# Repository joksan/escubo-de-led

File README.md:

# escubo-de-led
Un cubo de LED RGB de 4x4x4 en formato de escudo de Arduino

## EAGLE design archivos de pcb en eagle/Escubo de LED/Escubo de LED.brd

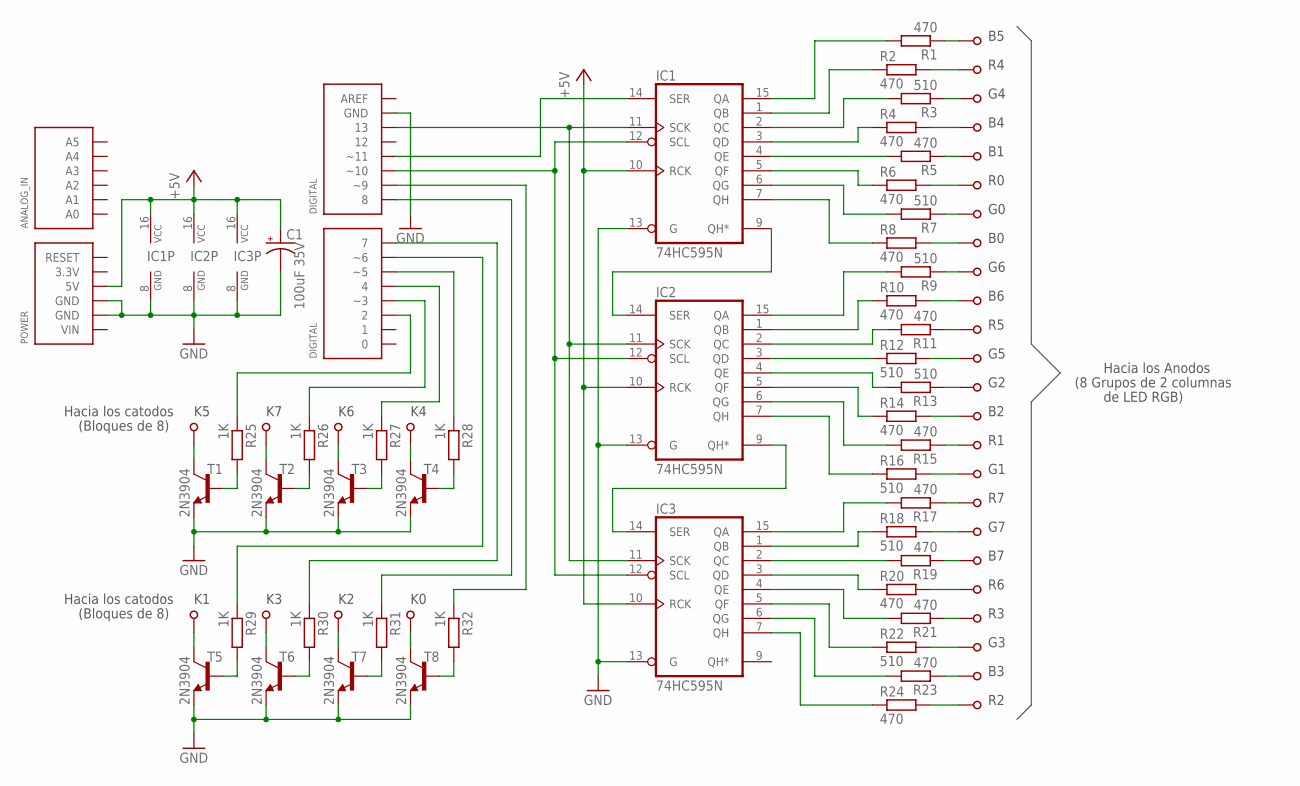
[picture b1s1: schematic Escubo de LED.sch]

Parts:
C1: 100uF 35V; E3,5-8
IC1, IC2, IC3: 74HC595N; DIP16
R1, R2, R4, R10, R11, R15, R17, R19, R20, R23: 470; 0204/7
R3, R7, R9, R12, R18: 510; 0204/7
R5, R21: 470; 0207/12
R6, R14: 470; 0207/10
R8, R24: 470; 0204/5
R13: 510; 0207/12
R16: 510; 0204/5
R22: 510; 0207/10
R25, R26, R27, R28, R29, R30, R31, R32: 1K; 0204V
S1: ARDUINO_SHIELD
T1, T2, T3, T4, T5, T6, T7, T8: 2N3904; TO92-EBC
U$1, U$2, U$3, U$4, U$5, U$6, U$7, U$8, U$9, U$10, U$11, U$12, U$13, U$14, U$15, U$16, U$17, U$18, U$19, U$20, U$21, U$22, U$23, U$24, U$25, U$26, U$27, U$28, U$29, U$30, U$31, U$32: PAD_SIMPLE_PTH

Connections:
+5V: C1.+, IC1.10 (RCK), IC1.16 (VCC), IC2.10 (RCK), IC2.16 (VCC), IC3.10 (RCK), IC3.16 (VCC), S1.5V
GND: C1.-, IC1.8 (GND), IC1.13 (G), IC2.8 (GND), IC2.13 (G), IC3.8 (GND), IC3.13 (G), S1.GND, S1.GND@1 (GND), S1.GND@2 (GND), T1.E, T2.E, T3.E, T4.E, T5.E, T6.E, T7.E, T8.E
unnamed: IC1.9 (QH*), IC2.14 (SER)
unnamed: IC2.9 (QH*), IC3.14 (SER)
unnamed: IC1.11 (SCK), IC2.11 (SCK), IC3.11 (SCK), S1.13
unnamed: IC1.14 (SER), S1.~11
unnamed: IC1.12 (SCL), IC2.12 (SCL), IC3.12 (SCL), S1.~10
unnamed: IC1.15 (QA), R1.2
unnamed: IC1.1 (QB), R2.1
unnamed: IC1.2 (QC), R3.2
unnamed: IC1.3 (QD), R4.1
unnamed: IC1.4 (QE), R5.2
unnamed: IC1.5 (QF), R6.1
unnamed: IC1.6 (QG), R7.2
unnamed: IC1.7 (QH), R8.1
unnamed: IC2.15 (QA), R9.2
unnamed: IC2.1 (QB), R10.1
unnamed: IC2.2 (QC), R11.2
unnamed: IC2.3 (QD), R12.1
unnamed: IC2.4 (QE), R13.2
unnamed: IC2.5 (QF), R14.1
unnamed: IC2.6 (QG), R15.2
unnamed: IC2.7 (QH), R16.1
unnamed: IC3.15 (QA), R17.2
unnamed: IC3.1 (QB), R18.1
unnamed: IC3.2 (QC), R19.2
unnamed: IC3.3 (QD), R20.1
unnamed: IC3.4 (QE), R21.2
unnamed: IC3.5 (QF), R22.1
unnamed: IC3.6 (QG), R23.2
unnamed: IC3.7 (QH), R24.1
unnamed: R1.1, U$1.P$1
unnamed: R2.2, U$2.P$1
unnamed: R3.1, U$3.P$1
unnamed: R4.2, U$4.P$1
unnamed: R6.2, U$6.P$1
unnamed: R8.2, U$8.P$1
unnamed: R10.2, U$10.P$1
unnamed: R12.2, U$12.P$1
unnamed: R14.2, U$14.P$1
unnamed: R16.2, U$16.P$1
unnamed: R18.2, U$18.P$1
unnamed: R20.2, U$20.P$1
unnamed: R22.2, U$22.P$1
unnamed: R24.2, U$24.P$1
unnamed: R5.1, U$5.P$1
unnamed: R7.1, U$7.P$1
unnamed: R9.1, U$9.P$1
unnamed: R11.1, U$11.P$1
unnamed: R13.1, U$13.P$1
unnamed: R15.1, U$15.P$1
unnamed: R17.1, U$17.P$1
unnamed: R19.1, U$19.P$1
unnamed: R21.1, U$21.P$1
unnamed: R23.1, U$23.P$1
unnamed: R25.1, S1.2
unnamed: R26.1, S1.~3
unnamed: R27.1, S1.4
unnamed: R28.1, S1.~5
unnamed: R29.1, S1.~6
unnamed: R30.1, S1.7
unnamed: R31.1, S1.8
unnamed: R32.1, S1.~9
unnamed: T1.C, U$25.P$1
unnamed: T2.C, U$26.P$1
unnamed: T3.C, U$27.P$1
unnamed: T4.C, U$28.P$1
unnamed: T5.C, U$29.P$1
unnamed: T6.C, U$30.P$1
unnamed: T7.C, U$31.P$1
unnamed: T8.C, U$32.P$1
unnamed: R25.2, T1.B
unnamed: R26.2, T2.B
unnamed: R27.2, T3.B
unnamed: R28.2, T4.B
unnamed: R29.2, T5.B
unnamed: R30.2, T6.B
unnamed: R31.2, T7.B
unnamed: R32.2, T8.B

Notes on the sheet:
Hacia los catodos
(Bloques de 8)
Hacia los Anodos
(8 Grupos de 2 columnas
de LED RGB)

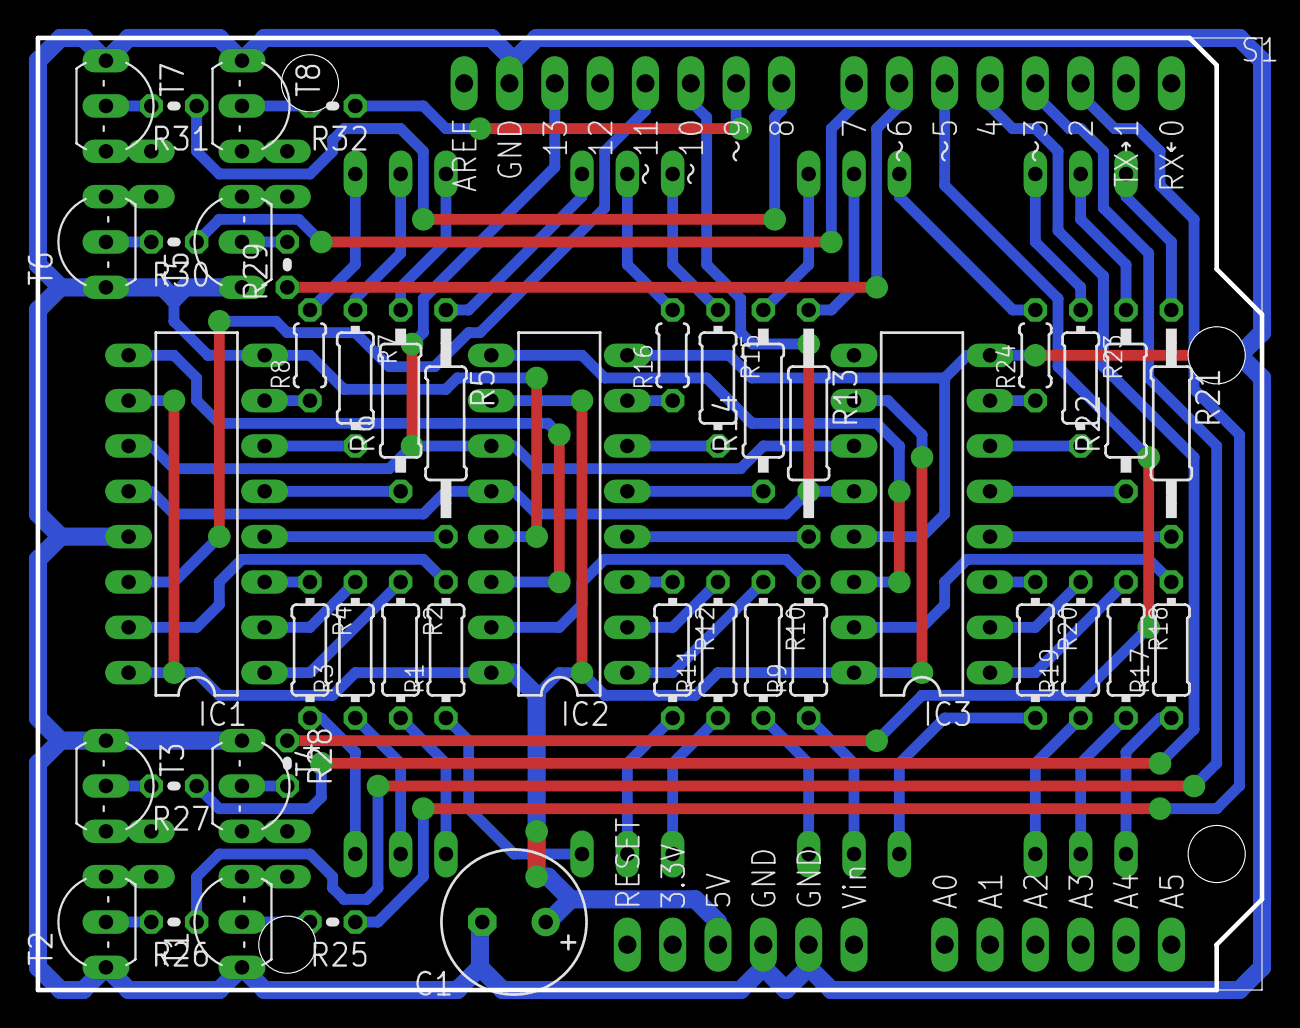
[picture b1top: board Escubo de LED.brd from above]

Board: 2 copper layers, 68.6 x 53.3 mm, 77 parts (0 on the bottom side), 79 nets.

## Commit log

2015-10-02 Agregados los archivos del proyecto
2017-10-27 Agregando GPL3.0 al código
